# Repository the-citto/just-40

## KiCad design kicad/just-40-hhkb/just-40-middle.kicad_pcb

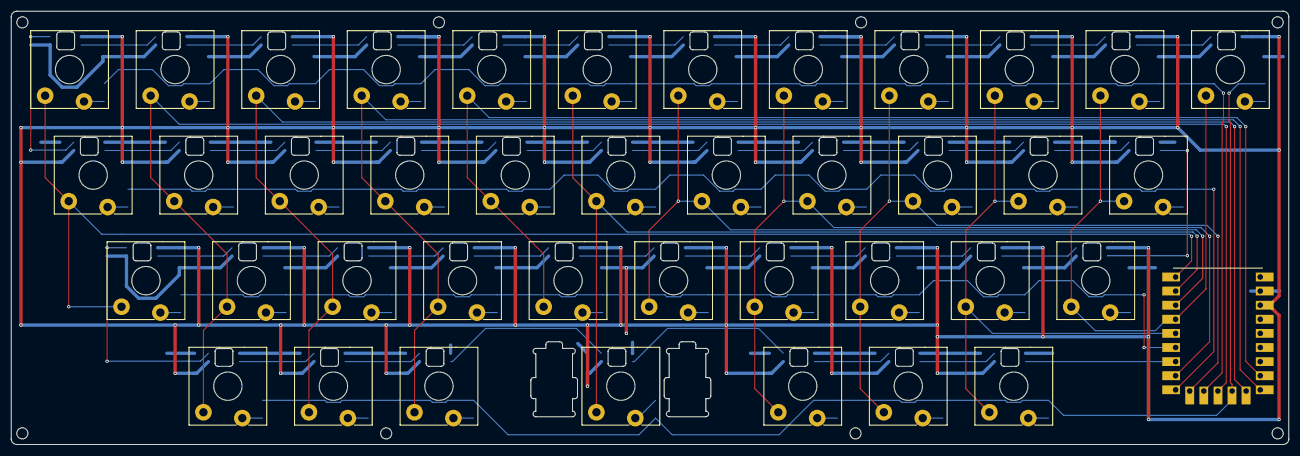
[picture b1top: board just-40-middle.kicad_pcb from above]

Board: 2 copper layers, 230.0 x 78.0 mm, 50 parts (0 on the bottom side), 97 nets.

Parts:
A1, A2, A3, A4, A5, A6, A7, A8, A9, A10, A11, A12, A24, A25, A26, A27, A28, A29, A30, A31, A32, A33: KB-SW-right; KB-SW-1U-right
A13, A14, A15, A16, A17, A18, A19, A20, A21, A22, A23, A34, A35, A36, A38, A39, A40: KB-SW-left; KB-SW-1U-left
A37: KB-SW-left; KB-SW-2.25U-left
A41: RP2350-Tiny; RP2350-Tiny-THT
H1, H2, H3, H4, H5, H6, H7, H8: mount-hole; Mount-Hole
H18: RP2350-Tiny-USB; RP2350-Tiny-USB-ref

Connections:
COL_00: A1.A, A13.A, A24.A, A41.0 (GPIO0)
COL_01: A2.A, A14.A, A25.A, A34.A, A41.11 (GPIO11)
COL_02: A3.A, A15.A, A26.A, A35.A, A41.13 (GPIO13)
COL_03: A4.A, A16.A, A27.A, A36.A, A41.14 (GPIO14)
COL_04: A5.A, A17.A, A28.A, A41.15 (GPIO15)
COL_05: A6.A, A18.A, A37.A, A41.1 (GPIO1)
COL_06: A7.A, A19.A, A29.A, A41.2 (GPIO2)
COL_07: A8.A, A20.A, A30.A, A38.A, A41.7 (GPIO7)
COL_08: A9.A, A21.A, A31.A, A39.A, A41.9 (GPIO9)
COL_09: A10.A, A22.A, A32.A, A40.A, A41.4 (GPIO4)
COL_10: A11.A, A12.A, A23.A, A33.A, A41.3 (GPIO3)
DIN: A40.4 (DIN), A41.6 (GPIO6)
GND: A1.3 (GND), A1.C_1, A2.3 (GND), A2.C_1, A3.3 (GND), A3.C_1, A4.3 (GND), A4.C_1, A5.3 (GND), A5.C_1, A6.3 (GND), A6.C_1, A7.3 (GND), A7.C_1, A8.3 (GND), A8.C_1, A9.3 (GND), A9.C_1, A10.3 (GND), A10.C_1, A11.3 (GND), A11.C_1, A12.3 (GND), A12.C_1, A13.3 (GND), A13.C_2, A14.3 (GND), A14.C_2, A15.3 (GND), A15.C_2, A16.3 (GND), A16.C_2, A17.3 (GND), A17.C_2, A18.3 (GND), A18.C_2, A19.3 (GND), A19.C_2, A20.3 (GND), A20.C_2, A21.3 (GND), A21.C_2, A22.3 (GND), A22.C_2, A23.3 (GND), A23.C_2, A24.3 (GND), A24.C_1, A25.3 (GND), A25.C_1, A26.3 (GND), A26.C_1, A27.3 (GND), A27.C_1, A28.3 (GND), A28.C_1, A29.3 (GND), A29.C_1, A30.3 (GND), A30.C_1, A31.3 (GND), A31.C_1, A32.3 (GND), A32.C_1, A33.3 (GND), A33.C_1, A34.3 (GND), A34.C_2, A35.3 (GND), A35.C_2, A36.3 (GND), A36.C_2, A37.3 (GND), A37.C_2, A38.3 (GND), A38.C_2, A39.3 (GND), A39.C_2, A40.3 (GND), A40.C_2, A41.GND
unnamed: A1.4 (DIN), A13.2 (DOUT)
unnamed: A1.2 (DOUT), A2.4 (DIN)
unnamed: A1.B, A1.D_1
unnamed: A2.2 (DOUT), A3.4 (DIN)
unnamed: A2.B, A2.D_1
unnamed: A3.2 (DOUT), A4.4 (DIN)
unnamed: A3.B, A3.D_1
unnamed: A4.2 (DOUT), A5.4 (DIN)
unnamed: A4.B, A4.D_1
unnamed: A5.2 (DOUT), A6.4 (DIN)
unnamed: A5.B, A5.D_1
unnamed: A6.2 (DOUT), A7.4 (DIN)
unnamed: A6.B, A6.D_1
unnamed: A7.2 (DOUT), A8.4 (DIN)
unnamed: A7.B, A7.D_1
unnamed: A8.2 (DOUT), A9.4 (DIN)
unnamed: A8.B, A8.D_1
unnamed: A9.B, A9.D_1
unnamed: A9.2 (DOUT), A10.4 (DIN)
unnamed: A10.2 (DOUT), A11.4 (DIN)
unnamed: A10.B, A10.D_1
unnamed: A11.2 (DOUT), A12.4 (DIN)
unnamed: A11.B, A11.D_1
unnamed: A12.B, A12.D_1
unnamed: A13.4 (DIN), A14.2 (DOUT)
unnamed: A13.B, A13.D_1
unnamed: A14.4 (DIN), A15.2 (DOUT)
unnamed: A14.B, A14.D_1
unnamed: A15.4 (DIN), A16.2 (DOUT)
unnamed: A15.B, A15.D_1
unnamed: A16.4 (DIN), A17.2 (DOUT)
unnamed: A16.B, A16.D_1
unnamed: A17.4 (DIN), A18.2 (DOUT)
unnamed: A17.B, A17.D_1
unnamed: A18.4 (DIN), A19.2 (DOUT)
unnamed: A18.B, A18.D_1
unnamed: A19.4 (DIN), A20.2 (DOUT)
unnamed: A19.B, A19.D_1
unnamed: A20.4 (DIN), A21.2 (DOUT)
unnamed: A20.B, A20.D_1
unnamed: A21.4 (DIN), A22.2 (DOUT)
unnamed: A21.B, A21.D_1
unnamed: A22.4 (DIN), A23.2 (DOUT)
unnamed: A22.B, A22.D_1
unnamed: A23.4 (DIN), A33.2 (DOUT)
unnamed: A23.B, A23.D_1
unnamed: A24.4 (DIN), A34.2 (DOUT)
unnamed: A24.2 (DOUT), A25.4 (DIN)
unnamed: A24.B, A24.D_1
unnamed: A25.2 (DOUT), A26.4 (DIN)
unnamed: A25.B, A25.D_1
unnamed: A26.2 (DOUT), A27.4 (DIN)
unnamed: A26.B, A26.D_1
unnamed: A27.2 (DOUT), A28.4 (DIN)
unnamed: A27.B, A27.D_1
unnamed: A28.2 (DOUT), A29.4 (DIN)
unnamed: A28.B, A28.D_1
unnamed: A29.2 (DOUT), A30.4 (DIN)
unnamed: A29.B, A29.D_1
unnamed: A30.2 (DOUT), A31.4 (DIN)
unnamed: A30.B, A30.D_1
unnamed: A31.2 (DOUT), A32.4 (DIN)
unnamed: A31.B, A31.D_1
unnamed: A32.2 (DOUT), A33.4 (DIN)
unnamed: A32.B, A32.D_1
unnamed: A33.B, A33.D_1
unnamed: A34.4 (DIN), A35.2 (DOUT)
unnamed: A34.B, A34.D_1
unnamed: A35.4 (DIN), A36.2 (DOUT)
unnamed: A35.B, A35.D_1
unnamed: A36.4 (DIN), A37.2 (DOUT)
unnamed: A36.B, A36.D_1
unnamed: A37.4 (DIN), A38.2 (DOUT)
unnamed: A37.B, A37.D_1
unnamed: A38.4 (DIN), A39.2 (DOUT)
unnamed: A38.B, A38.D_1
unnamed: A39.4 (DIN), A40.2 (DOUT)
unnamed: A39.B, A39.D_1
unnamed: A40.B, A40.D_1
ROW_0: A1.D_2, A2.D_2, A3.D_2, A4.D_2, A5.D_2, A6.D_2, A7.D_2, A8.D_2, A9.D_2, A10.D_2, A11.D_2, A41.10 (GPIO10)
ROW_1: A13.D_2, A14.D_2, A15.D_2, A16.D_2, A17.D_2, A18.D_2, A19.D_2, A20.D_2, A21.D_2, A22.D_2, A23.D_2, A41.8 (GPIO8)
ROW_2: A24.D_2, A25.D_2, A26.D_2, A27.D_2, A28.D_2, A29.D_2, A30.D_2, A31.D_2, A32.D_2, A33.D_2, A41.5 (GPIO5)
ROW_3: A12.D_2, A34.D_2, A35.D_2, A36.D_2, A37.D_2, A38.D_2, A39.D_2, A40.D_2, A41.12 (GPIO12)
V_LED: A1.1 (VDD), A1.C_2, A2.1 (VDD), A2.C_2, A3.1 (VDD), A3.C_2, A4.1 (VDD), A4.C_2, A5.1 (VDD), A5.C_2, A6.1 (VDD), A6.C_2, A7.1 (VDD), A7.C_2, A8.1 (VDD), A8.C_2, A9.1 (VDD), A9.C_2, A10.1 (VDD), A10.C_2, A11.1 (VDD), A11.C_2, A12.1 (VDD), A12.C_2, A13.1 (VDD), A13.C_1, A14.1 (VDD), A14.C_1, A15.1 (VDD), A15.C_1, A16.1 (VDD), A16.C_1, A17.1 (VDD), A17.C_1, A18.1 (VDD), A18.C_1, A19.1 (VDD), A19.C_1, A20.1 (VDD), A20.C_1, A21.1 (VDD), A21.C_1, A22.1 (VDD), A22.C_1, A23.1 (VDD), A23.C_1, A24.1 (VDD), A24.C_2, A25.1 (VDD), A25.C_2, A26.1 (VDD), A26.C_2, A27.1 (VDD), A27.C_2, A28.1 (VDD), A28.C_2, A29.1 (VDD), A29.C_2, A30.1 (VDD), A30.C_2, A31.1 (VDD), A31.C_2, A32.1 (VDD), A32.C_2, A33.1 (VDD), A33.C_2, A34.1 (VDD), A34.C_1, A35.1 (VDD), A35.C_1, A36.1 (VDD), A36.C_1, A37.1 (VDD), A37.C_1, A38.1 (VDD), A38.C_1, A39.1 (VDD), A39.C_1, A40.1 (VDD), A40.C_1, A41.3V3

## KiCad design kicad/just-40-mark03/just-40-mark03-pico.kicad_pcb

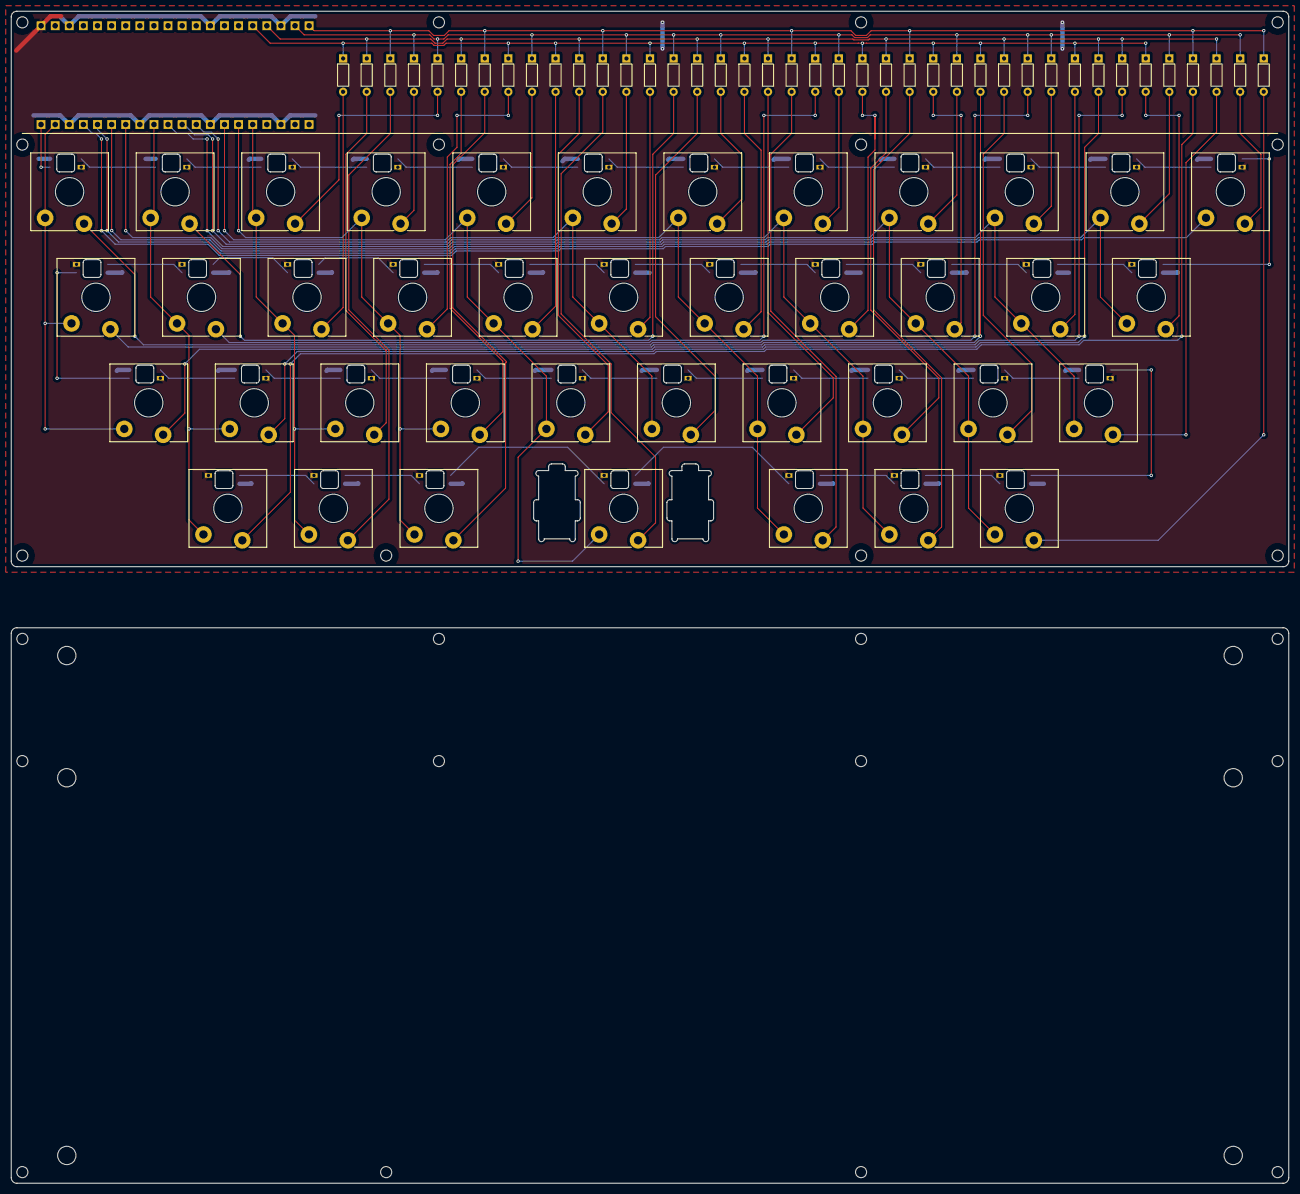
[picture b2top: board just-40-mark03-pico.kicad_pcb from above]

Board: 2 copper layers, 230.0 x 100.0 mm, 111 parts (0 on the bottom side), 98 nets.

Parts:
A1, A2, A3, A4, A5, A6, A7, A8, A9, A10, A11, A12, A24, A25, A26, A27, A28, A29, A30, A31, A32, A33: KS-33-1U-LED-right
A13, A14, A15, A16, A17, A18, A19, A20, A21, A22, A23, A34, A35, A36, A38, A39, A40: KS-33-1U-LED-left
A37: KS-33-1U-LED-left; KS-33-2.25U-LED-left
D1, D2, D3, D4, D5, D6, D7, D8, D9, D10, D11, D12, D13, D14, D15, D16, D17, D18, D19, D20, D21, D22, D23, D24, D25, D26, D27, D28, D29, D30, D31, D32, D33, D34, D35, D36, D37, D38, D39, D40: 1N4148
H1, H2, H3, H4, H5, H6: hole-foot
H7, H8, H9, H10, H11, H12, H13, H14, H15, H16, H17, H18, H19, H20, H21, H22, H23, H24, H25, H26, H27, H28, H29, H30: hole-mount
U1: PICO-2

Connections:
COL_00: A1.A, A13.A, A24.A, U1.2 (GPIO1)
COL_01: A2.A, A14.A, A25.A, A34.A, U1.9 (GPIO6)
COL_02: A3.A, A15.A, A26.A, A35.A, U1.16 (GPIO12)
COL_03: A4.A, A16.A, A27.A, A36.A, U1.15 (GPIO11)
COL_04: A5.A, A17.A, A28.A, A37.A, U1.14 (GPIO10)
COL_05: A6.A, A18.A, A29.A, U1.12 (GPIO9)
COL_06: A7.A, A19.A, A30.A, A38.A, U1.11 (GPIO8)
COL_07: A8.A, A20.A, A31.A, A39.A, U1.10 (GPIO7)
COL_08: A9.A, A21.A, A32.A, A40.A, U1.7 (GPIO5)
COL_09: A10.A, A22.A, A33.A, U1.6 (GPIO4)
COL_10: A11.A, A23.A, U1.5 (GPIO3)
COL_11: A12.A, U1.4 (GPIO2)
DIN: A1.4 (DIN), U1.1 (GPIO0)
GND: A1.3 (GND), A2.3 (GND), A3.3 (GND), A4.3 (GND), A5.3 (GND), A6.3 (GND), A7.3 (GND), A8.3 (GND), A9.3 (GND), A10.3 (GND), A11.3 (GND), A12.3 (GND), A13.3 (GND), A14.3 (GND), A15.3 (GND), A16.3 (GND), A17.3 (GND), A18.3 (GND), A19.3 (GND), A20.3 (GND), A21.3 (GND), A22.3 (GND), A23.3 (GND), A24.3 (GND), A25.3 (GND), A26.3 (GND), A27.3 (GND), A28.3 (GND), A29.3 (GND), A30.3 (GND), A31.3 (GND), A32.3 (GND), A33.3 (GND), A34.3 (GND), A35.3 (GND), A36.3 (GND), A37.3 (GND), A38.3 (GND), A39.3 (GND), A40.3 (GND), U1.3 (GND), U1.8 (GND), U1.13 (GND), U1.18 (GND), U1.23 (GND), U1.28 (GND), U1.38 (GND)
unnamed: A1.2 (DOUT), A2.4 (DIN)
unnamed: A2.2 (DOUT), A3.4 (DIN)
unnamed: A3.2 (DOUT), A4.4 (DIN)
unnamed: A4.2 (DOUT), A5.4 (DIN)
unnamed: A5.2 (DOUT), A6.4 (DIN)
unnamed: A6.2 (DOUT), A7.4 (DIN)
unnamed: A7.2 (DOUT), A8.4 (DIN)
unnamed: A8.2 (DOUT), A9.4 (DIN)
unnamed: A9.2 (DOUT), A10.4 (DIN)
unnamed: A10.2 (DOUT), A11.4 (DIN)
unnamed: A11.2 (DOUT), A12.4 (DIN)
unnamed: A12.2 (DOUT), A23.4 (DIN)
unnamed: A13.4 (DIN), A14.2 (DOUT)
unnamed: A13.2 (DOUT), A24.4 (DIN)
unnamed: A14.4 (DIN), A15.2 (DOUT)
unnamed: A15.4 (DIN), A16.2 (DOUT)
unnamed: A16.4 (DIN), A17.2 (DOUT)
unnamed: A17.4 (DIN), A18.2 (DOUT)
unnamed: A18.4 (DIN), A19.2 (DOUT)
unnamed: A19.4 (DIN), A20.2 (DOUT)
unnamed: A20.4 (DIN), A21.2 (DOUT)
unnamed: A21.4 (DIN), A22.2 (DOUT)
unnamed: A22.4 (DIN), A23.2 (DOUT)
unnamed: A24.2 (DOUT), A25.4 (DIN)
unnamed: A25.2 (DOUT), A26.4 (DIN)
unnamed: A26.2 (DOUT), A27.4 (DIN)
unnamed: A27.2 (DOUT), A28.4 (DIN)
unnamed: A28.2 (DOUT), A29.4 (DIN)
unnamed: A29.2 (DOUT), A30.4 (DIN)
unnamed: A30.2 (DOUT), A31.4 (DIN)
unnamed: A31.2 (DOUT), A32.4 (DIN)
unnamed: A32.2 (DOUT), A33.4 (DIN)
unnamed: A33.2 (DOUT), A40.4 (DIN)
unnamed: A34.4 (DIN), A35.2 (DOUT)
unnamed: A35.4 (DIN), A36.2 (DOUT)
unnamed: A36.4 (DIN), A37.2 (DOUT)
unnamed: A37.4 (DIN), A38.2 (DOUT)
unnamed: A38.4 (DIN), A39.2 (DOUT)
unnamed: A39.4 (DIN), A40.2 (DOUT)
unnamed: A1.B, D1.2 (A)
unnamed: A2.B, D2.2 (A)
unnamed: A3.B, D3.2 (A)
unnamed: A4.B, D4.2 (A)
unnamed: A5.B, D5.2 (A)
unnamed: A6.B, D6.2 (A)
unnamed: A7.B, D7.2 (A)
unnamed: A8.B, D8.2 (A)
unnamed: A9.B, D9.2 (A)
unnamed: A10.B, D10.2 (A)
unnamed: A11.B, D11.2 (A)
unnamed: A12.B, D12.2 (A)
unnamed: A13.B, D13.2 (A)
unnamed: A14.B, D14.2 (A)
unnamed: A15.B, D15.2 (A)
unnamed: A16.B, D16.2 (A)
unnamed: A17.B, D17.2 (A)
unnamed: A18.B, D18.2 (A)
unnamed: A19.B, D19.2 (A)
unnamed: A20.B, D20.2 (A)
unnamed: A21.B, D21.2 (A)
unnamed: A22.B, D22.2 (A)
unnamed: A23.B, D23.2 (A)
unnamed: A24.B, D24.2 (A)
unnamed: A25.B, D25.2 (A)
unnamed: A26.B, D26.2 (A)
unnamed: A27.B, D27.2 (A)
unnamed: A28.B, D28.2 (A)
unnamed: A29.B, D29.2 (A)
unnamed: A30.B, D30.2 (A)
unnamed: A31.B, D31.2 (A)
unnamed: A32.B, D32.2 (A)
unnamed: A33.B, D33.2 (A)
unnamed: A34.B, D34.2 (A)
unnamed: A35.B, D35.2 (A)
unnamed: A36.B, D36.2 (A)
unnamed: A37.B, D37.2 (A)
unnamed: A38.B, D38.2 (A)
unnamed: A39.B, D39.2 (A)
unnamed: A40.B, D40.2 (A)
ROW_0: D1.1 (K), D2.1 (K), D3.1 (K), D4.1 (K), D5.1 (K), D6.1 (K), D7.1 (K), D8.1 (K), D9.1 (K), D10.1 (K), D11.1 (K), D12.1 (K), U1.22 (GPIO17)
ROW_1: D13.1 (K), D14.1 (K), D15.1 (K), D16.1 (K), D17.1 (K), D18.1 (K), D19.1 (K), D20.1 (K), D21.1 (K), D22.1 (K), D23.1 (K), U1.25 (GPIO19)
ROW_2: D24.1 (K), D25.1 (K), D26.1 (K), D27.1 (K), D28.1 (K), D29.1 (K), D30.1 (K), D31.1 (K), D32.1 (K), D33.1 (K), U1.24 (GPIO18)
ROW_3: D34.1 (K), D35.1 (K), D36.1 (K), D37.1 (K), D38.1 (K), D39.1 (K), D40.1 (K), U1.21 (GPIO16)
V_LED: A1.1 (VDD), A2.1 (VDD), A3.1 (VDD), A4.1 (VDD), A5.1 (VDD), A6.1 (VDD), A7.1 (VDD), A8.1 (VDD), A9.1 (VDD), A10.1 (VDD), A11.1 (VDD), A12.1 (VDD), A13.1 (VDD), A14.1 (VDD), A15.1 (VDD), A16.1 (VDD), A17.1 (VDD), A18.1 (VDD), A19.1 (VDD), A20.1 (VDD), A21.1 (VDD), A22.1 (VDD), A23.1 (VDD), A24.1 (VDD), A25.1 (VDD), A26.1 (VDD), A27.1 (VDD), A28.1 (VDD), A29.1 (VDD), A30.1 (VDD), A31.1 (VDD), A32.1 (VDD), A33.1 (VDD), A34.1 (VDD), A35.1 (VDD), A36.1 (VDD), A37.1 (VDD), A38.1 (VDD), A39.1 (VDD), A40.1 (VDD), U1.40 (VBUS)
